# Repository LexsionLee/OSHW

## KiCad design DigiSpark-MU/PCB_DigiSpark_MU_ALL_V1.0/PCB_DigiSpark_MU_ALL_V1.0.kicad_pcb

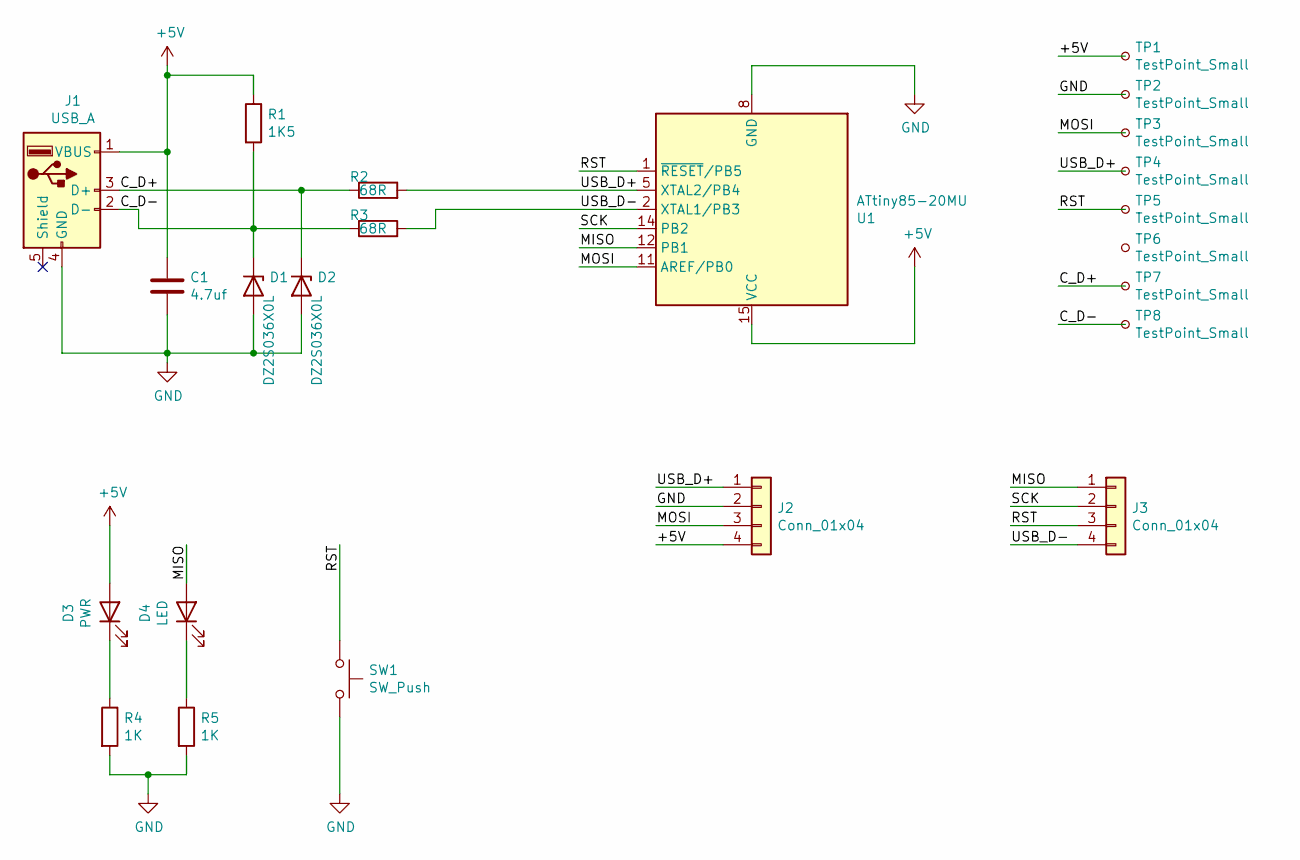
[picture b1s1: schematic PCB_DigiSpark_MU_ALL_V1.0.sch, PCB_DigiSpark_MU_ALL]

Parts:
C1: 4.7uf; C_0603_1608Metric
D1, D2: DZ2S036X0L; D_SOD-523
D3: PWR; LED_0603_1608Metric
D4: LED; LED_0603_1608Metric
J1: USB_A; PCBUSB_A_Male
J2, J3: Conn_01x04; Lex_Conn_Edge_2.54-4
R1: 1K5; R_0603_1608Metric
R2, R3: 68R; R_0603_1608Metric
R4, R5: 1K; R_0603_1608Metric
SW1: SW_Push; SW_SPST_SKQG_WithStem
TP1, TP2, TP3, TP4, TP5, TP6, TP7, TP8: TestPoint_Small; TestPoint_Pad_D1.0mm
U1: ATtiny85-20MU; QFN-20-1EP_4x4mm_P0.5mm_EP2.6x2.6mm

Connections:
+5V: C1.1, D3.2 (A), J1.1 (VBUS), J2.4, R1.1, TP1.1, U1.15 (VCC)
/C_D+: D2.1 (K), J1.3 (D+), R2.1, TP7.1
/C_D-: D1.1 (K), J1.2 (D-), R1.2, R3.1, TP8.1
/MISO: D4.2 (A), J3.1, U1.12 (PB1)
/MOSI: J2.3, TP3.1, U1.11 (AREF/PB0)
/RST: J3.3, SW1.1, TP5.1, U1.1 (~RESET~/PB5)
/SCK: J3.2, U1.14 (PB2)
/USB_D+: J2.1, R2.2, TP4.1, U1.5 (XTAL2/PB4)
/USB_D-: J3.4, R3.2, U1.2 (XTAL1/PB3)
GND: C1.2, D1.2 (A), D2.2 (A), J1.4 (GND), J2.2, R4.2, R5.2, SW1.2, TP2.1, U1.8 (GND), U1.21 (GND)
unnamed: D3.1 (K), R4.1
unnamed: D4.1 (K), R5.1

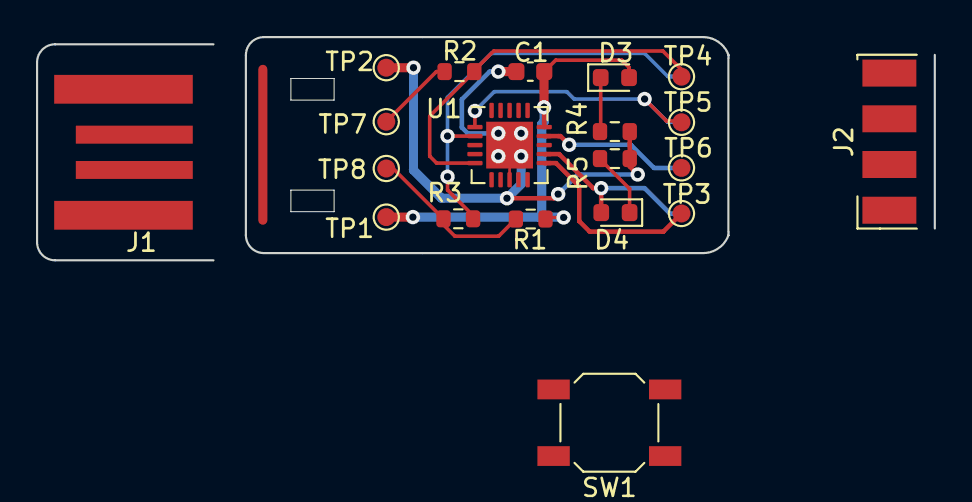
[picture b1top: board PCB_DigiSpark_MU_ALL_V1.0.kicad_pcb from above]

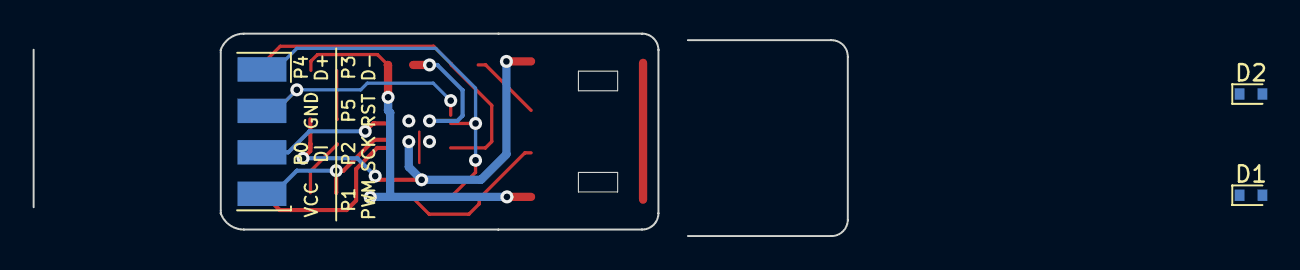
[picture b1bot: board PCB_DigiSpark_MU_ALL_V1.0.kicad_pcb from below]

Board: 2 copper layers, 49.9 x 12.4 mm, 23 parts (3 on the bottom side), 12 nets.
